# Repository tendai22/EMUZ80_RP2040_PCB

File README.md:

# EMUZ80_RP2040_PCB
A Z80 manipulator with Akizuki AE-RP2040 / or 2350A compatibles

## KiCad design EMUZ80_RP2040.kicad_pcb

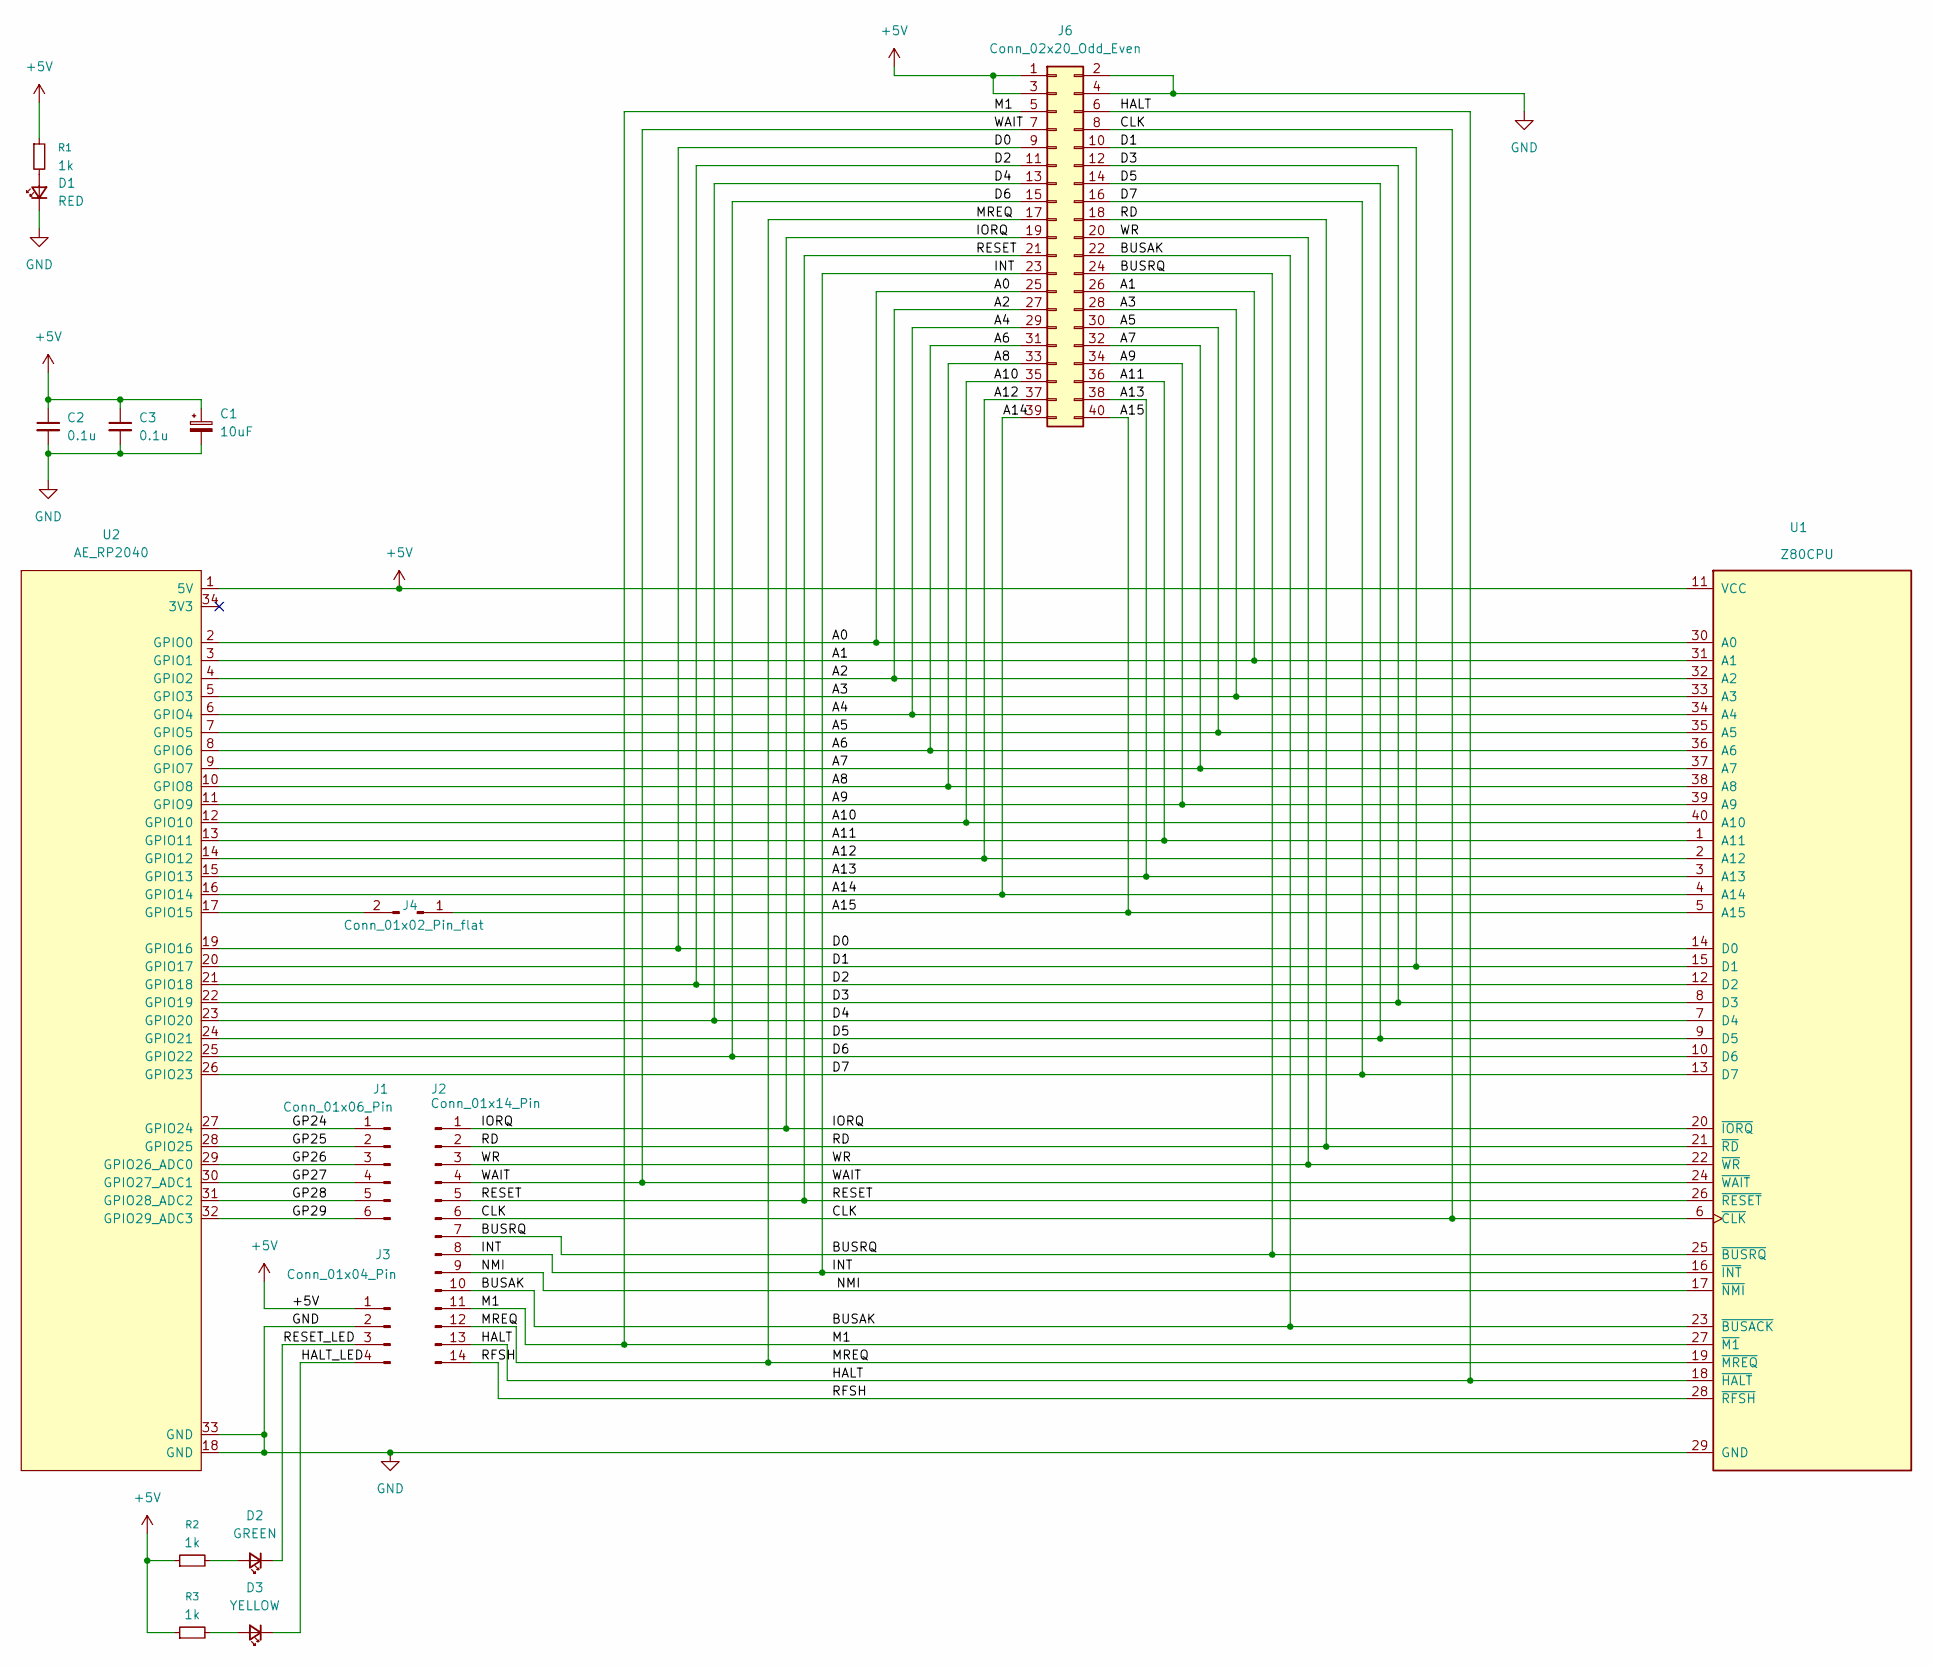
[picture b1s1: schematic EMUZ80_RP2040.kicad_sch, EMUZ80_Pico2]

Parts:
C1: 10uF; CP_Radial_D5.0mm_P2.50mm
C2, C3: 0.1u; C_Disc_D3.0mm_W1.6mm_P2.50mm
D1: RED; LED_D3.0mm
D2: GREEN; LED_D3.0mm
D3: YELLOW; LED_D3.0mm
J1: Conn_01x06_Pin; PinHeader_1x06_P2.54mm_Vertical
J2: Conn_01x14_Pin; PinHeader_1x14_P2.54mm_Vertical
J3: Conn_01x04_Pin; PinHeader_1x04_P2.54mm_Vertical
J4: Conn_01x02_Pin_flat; PinHeader_1x02_P2.54mm_Vertical
J6: Conn_02x20_Odd_Even; PinSocket_2x20_OvalPad
R1, R2, R3: 1k; R_Axial_L5.5mm_D2.0mm_P7.62mm_Horizontal
U1: Z80CPU; DIP-40_SidePin_Z80
U2: AE_RP2040; DIP-34_SidePin_AE_RP2040

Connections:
+5V: C1.1, C2.1, C3.1, J3.1, J6.1, J6.3, R1.1, R2.1, R3.1, U1.11 (VCC), U2.1 (5V)
/A0: J6.25, U1.30 (A0), U2.2 (GPIO0)
/A1: J6.26, U1.31 (A1), U2.3 (GPIO1)
/A2: J6.27, U1.32 (A2), U2.4 (GPIO2)
/A3: J6.28, U1.33 (A3), U2.5 (GPIO3)
/A4: J6.29, U1.34 (A4), U2.6 (GPIO4)
/A5: J6.30, U1.35 (A5), U2.7 (GPIO5)
/A6: J6.31, U1.36 (A6), U2.8 (GPIO6)
/A7: J6.32, U1.37 (A7), U2.9 (GPIO7)
/A8: J6.33, U1.38 (A8), U2.10 (GPIO8)
/A9: J6.34, U1.39 (A9), U2.11 (GPIO9)
/A10: J6.35, U1.40 (A10), U2.12 (GPIO10)
/A11: J6.36, U1.1 (A11), U2.13 (GPIO11)
/A12: J6.37, U1.2 (A12), U2.14 (GPIO12)
/A13: J6.38, U1.3 (A13), U2.15 (GPIO13)
/A14: J6.39, U1.4 (A14), U2.16 (GPIO14)
/A15: J4.1, J6.40, U1.5 (A15)
/BUSAK: J2.10, J6.22, U1.23 (~BUSACK)
/BUSRQ: J2.7, J6.24, U1.25 (~BUSRQ)
/CLK: J2.6, J6.8, U1.6 (~CLK)
/D0: J6.9, U1.14 (D0), U2.19 (GPIO16)
/D1: J6.10, U1.15 (D1), U2.20 (GPIO17)
/D2: J6.11, U1.12 (D2), U2.21 (GPIO18)
/D3: J6.12, U1.8 (D3), U2.22 (GPIO19)
/D4: J6.13, U1.7 (D4), U2.23 (GPIO20)
/D5: J6.14, U1.9 (D5), U2.24 (GPIO21)
/D6: J6.15, U1.10 (D6), U2.25 (GPIO22)
/D7: J6.16, U1.13 (D7), U2.26 (GPIO23)
/GP24: J1.1, U2.27 (GPIO24)
/GP25: J1.2, U2.28 (GPIO25)
/GP26: J1.3, U2.29 (GPIO26_ADC0)
/GP27: J1.4, U2.30 (GPIO27_ADC1)
/GP28: J1.5, U2.31 (GPIO28_ADC2)
/GP29: J1.6, U2.32 (GPIO29_ADC3)
/HALT: J2.13, J6.6, U1.18 (~HALT)
/HALT_LED: D3.1 (K), J3.4
/INT: J2.8, J6.23, U1.16 (~INT)
/IORQ: J2.1, J6.19, U1.20 (~IORQ)
/M1: J2.11, J6.5, U1.27 (~M1)
/MREQ: J2.12, J6.17, U1.19 (~MREQ)
/NMI: J2.9, U1.17 (~NMI)
/RD: J2.2, J6.18, U1.21 (~RD)
/RESET: J2.5, J6.21, U1.26 (~RESET)
/RESET_LED: D2.1 (K), J3.3
/RFSH: J2.14, U1.28 (~RFSH)
/WAIT: J2.4, J6.7, U1.24 (~WAIT)
/WR: J2.3, J6.20, U1.22 (~WR)
GND: C1.2, C2.2, C3.2, D1.1 (K), J3.2, J6.2, J6.4, U1.29 (GND), U2.18 (GND), U2.33 (GND)
unnamed: D1.2 (A), R1.2
unnamed: D2.2 (A), R2.2
unnamed: D3.2 (A), R3.2
unnamed: J4.2, U2.17 (GPIO15)

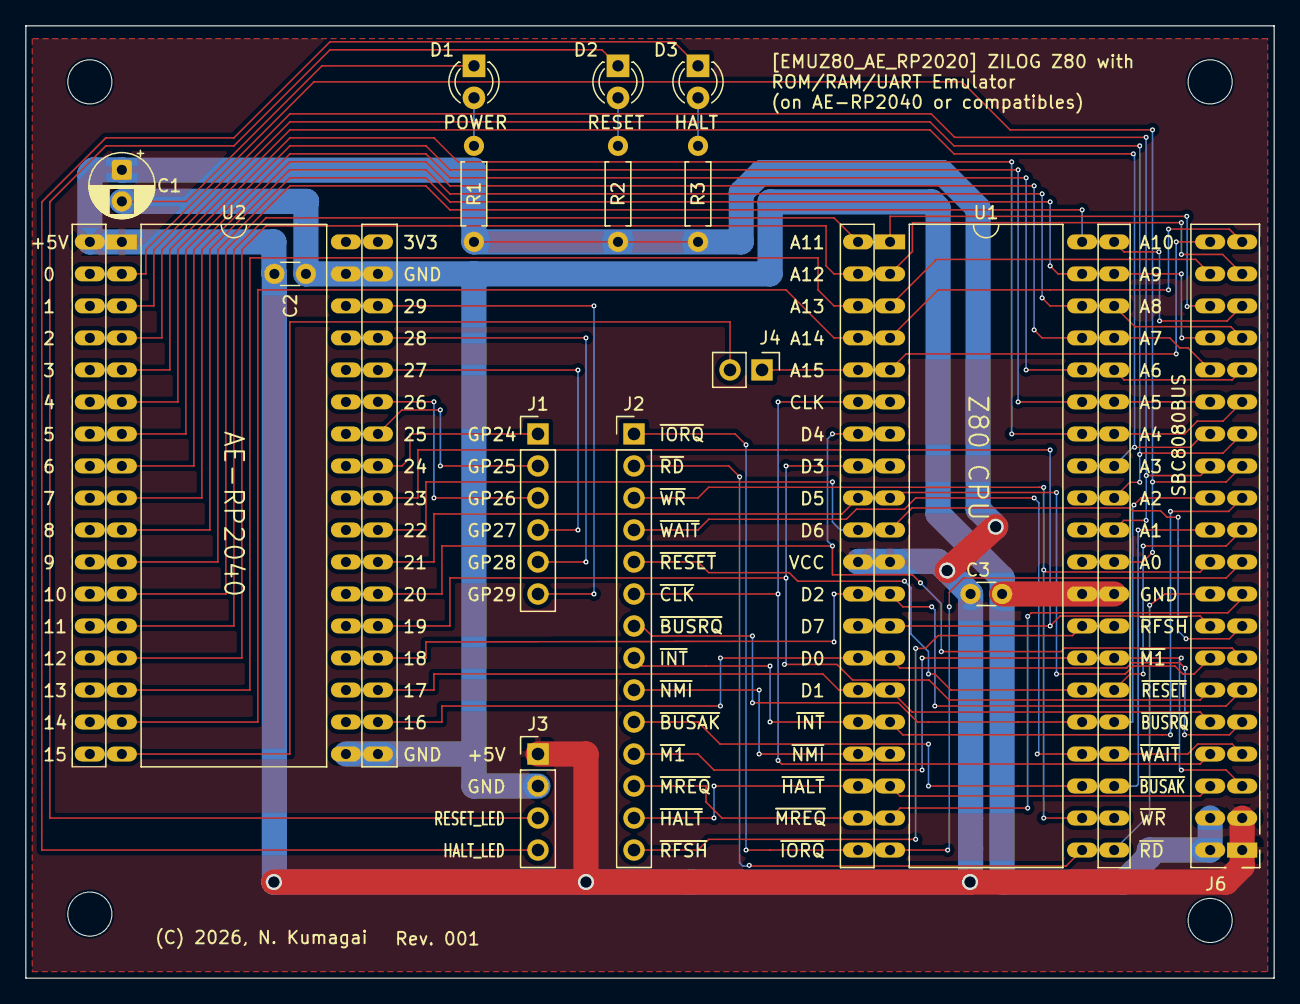
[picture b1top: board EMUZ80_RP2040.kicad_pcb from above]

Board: 2 copper layers, 99.1 x 75.6 mm, 20 parts (0 on the bottom side), 52 nets.

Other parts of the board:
H1, H2, H3, H3#2: MountingHole; MountingHole_3.5mm

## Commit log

2026-02-08 KiCad files added, PCB initial design done.
2026-02-09 main: AE-RP2040 version Rev001 garber finished

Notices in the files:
EMUZ80_RP2040.kicad_pcb:
(C) 2026, N. Kumagai
